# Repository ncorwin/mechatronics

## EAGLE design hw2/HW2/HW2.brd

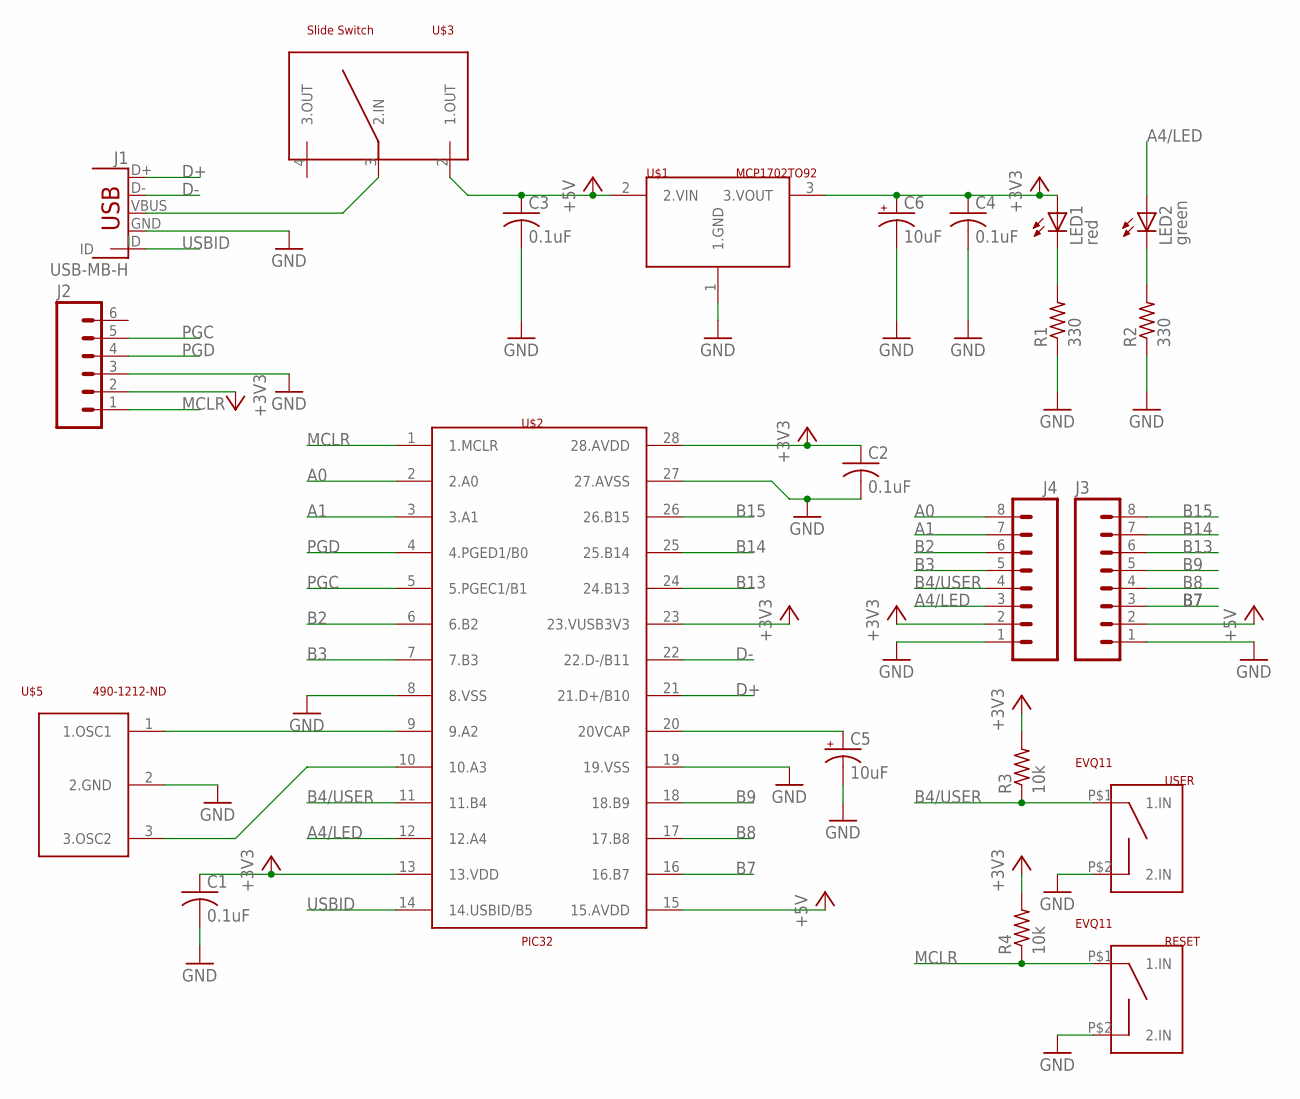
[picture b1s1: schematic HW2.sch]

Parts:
C1, C2, C3, C4: 0.1uF; C025-024X044
C5, C6: 10uF; B45181A
J1: USB-MB-H
J2: M06SILK_FEMALE_PTH; 1X06
J3, J4: M08SILK_FEMALE_PTH; 1X08
LED1: red; LED3MM
LED2: green; LED3MM
R1, R2: 330; 0204/7
R3, R4: 10k; 0204/7
RESET: EVQ11; 1X02_BIG
U$1: MCP1702TO92; TO92
U$2: PIC32; DIL28-3
U$3: A107673-ND; 1X05_NO_SILK
U$5: 490-1212-ND; 1X03_NO_SILK
USER: EVQ11; 1X02_BIG

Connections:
+3V3: C1.1, C2.1, C4.1, C6.+, J2.2, J4.2, LED1.A, R3.2, R4.2, U$1.3 (3.VOUT), U$2.13 (13.VDD), U$2.23 (23.VUSB3V3), U$2.28 (28.AVDD)
+5V: C3.1, J3.2, U$1.2 (2.VIN), U$2.15 (15.AVDD), U$3.2 (1.OUT)
A0: J4.8, U$2.2 (2.A0)
A1: J4.7, U$2.3 (3.A1)
A4/LED: J4.3, LED2.A, U$2.12 (12.A4)
B2: J4.6, U$2.6 (6.B2)
B3: J4.5, U$2.7 (7.B3)
B4/USER: J4.4, R3.1, U$2.11 (11.B4), USER.P$1 (1.IN)
B7: J3.3, U$2.16 (16.B7)
B8: J3.4, U$2.17 (17.B8)
B9: J3.5, U$2.18 (18.B9)
B13: J3.6, U$2.24 (24.B13)
B14: J3.7, U$2.25 (25.B14)
B15: J3.8, U$2.26 (26.B15)
D+: J1.D+, U$2.21 (21.D+/B10)
D-: J1.D-, U$2.22 (22.D-/B11)
GND: C1.2, C2.2, C3.2, C4.2, C5.-, C6.-, J1.GND, J2.3, J3.1, J4.1, R1.1, R2.1, RESET.P$2 (2.IN), U$1.1 (1.GND), U$2.8 (8.VSS), U$2.19 (19.VSS), U$2.27 (27.AVSS), U$5.2 (2.GND), USER.P$2 (2.IN)
MCLR: J2.1, R4.1, RESET.P$1 (1.IN), U$2.1 (1.MCLR)
unnamed: J1.VBUS, U$3.3 (2.IN)
unnamed: LED1.K (C), R1.2
unnamed: LED2.K (C), R2.2
unnamed: U$2.9 (9.A2), U$5.1 (1.OSC1)
unnamed: U$2.10 (10.A3), U$5.3 (3.OSC2)
unnamed: C5.+, U$2.20 (20VCAP)
PGC: J2.5, U$2.5 (5.PGEC1/B1)
PGD: J2.4, U$2.4 (4.PGED1/B0)
USBID: J1.ID, U$2.14 (14.USBID/B5)

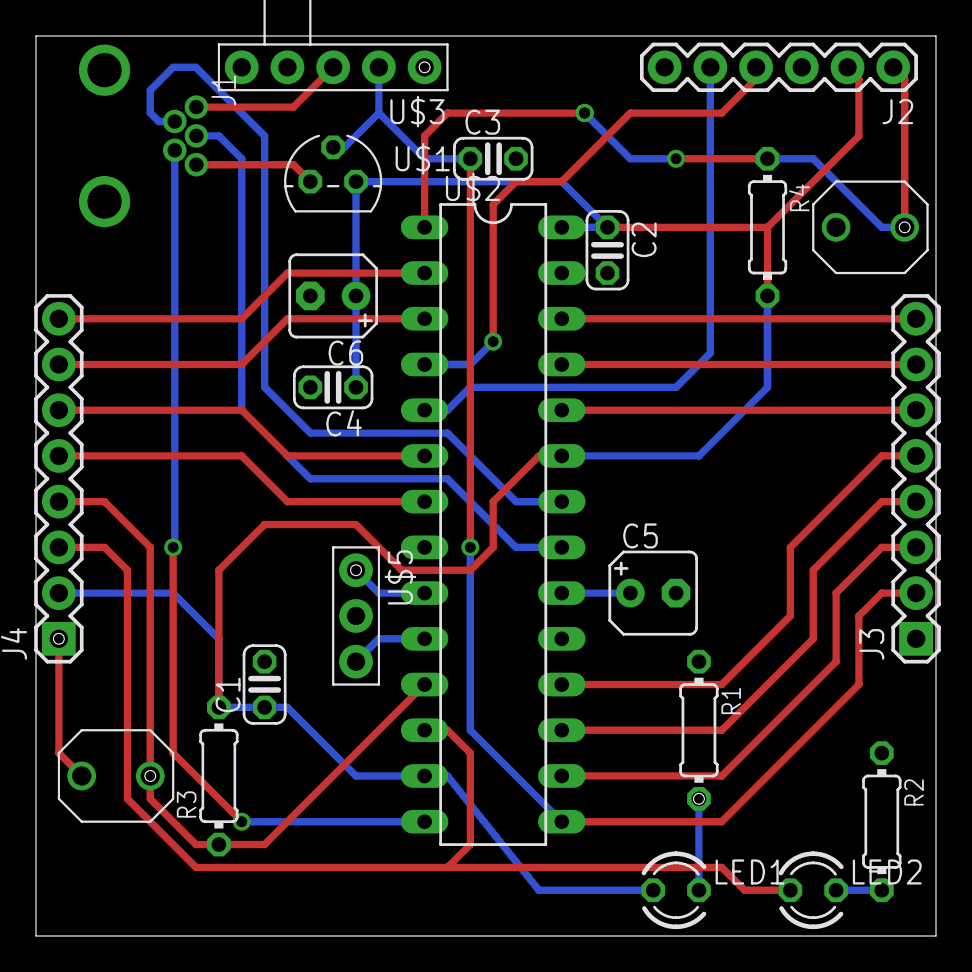
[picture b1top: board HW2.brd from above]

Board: 2 copper layers, 50.0 x 50.0 mm, 22 parts (0 on the bottom side), 27 nets.

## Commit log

2016-03-31 added screenshot of 3.3V power supply without caps
2016-03-31 added screenshot of 3.3V supply with caps. Oscilation stopped when 0.1 uF cap was added to regulator output
2016-04-02 Added picture of completed breadbord circuit
2016-04-02 Created main.c, can compile and upload but cant turn on LED
2016-04-02 still working on LED
2016-04-05 LED working, can toggle with pushbutton
2016-04-05 1 kHz toggle working, LED toggles at about 1 kHz, and turns on without toggling when pushbutton is depressed
2016-04-05 Pushbutton now pauses toggle at current LED output until released
2016-04-05 updated breadboard pic. Fixed wrong connection to crystal oscilator
2016-04-13 Created library for PCB
2016-04-14 Finished PCB schematic
2016-04-14 Working on .brd
2016-04-14 Finished .brd wiring
2016-04-14 Finished .brd
2016-04-14 Generated Gerber files
2016-04-14 Fixed Gerber files so it renders properly. zipped them into HW2.zip
2016-04-14 Added my name to the silkscreen layer
2016-04-14 Ready to be checked before order
2016-04-25 Created hw4 and started modifying example code
2016-04-25 Proboably finished spi.c
2016-04-25 created h file for configuring pic
2016-04-25 added waveform output to main.c
2016-04-25 it's not working
2016-04-25 it's still not working but I made separate .c and .h files for spi and i2c
2016-04-25 nothing's working. I give up
2016-04-25 spi is working, added nscope output pic
2016-04-25 fixed speed of DAC outputs
2016-04-26 working on I2C
2016-04-26 I2C still not working
2016-04-27 still working on I2C
2016-04-28 I2C working!
2016-04-28 Added pictures of hw4 circuit, made a pictures folder
2016-05-11 working on LCD
2016-05-11 still working on LCD
2016-05-12 hw5 LCD is working
2016-05-13 working on IMU
2016-05-14 still working on IMU, reading whoami wut not actual values
2016-05-16 still working on IMU
2016-05-17 IMU working
2016-05-17 added pictures to hw5, hw5 complete
2016-05-17 output OC1 and OC2 PWMs as functions of x and y accelration. Added picture of PWMs to repo. COmpleted hw6
2016-05-24 working on hw12, added code from repo, app crashes immediatly
2016-05-24 did hw9, FYI all android homeworks are in folders under android_projects/
2016-05-24 working on hw12, android camera line tracking, app still crashes immeadiatly
2016-05-29 created stl for wheel
2016-05-29 hw12 working for b&w image
2016-06-01 finished hw7, imu mouse
2016-06-01 completed hw8, CDC
2016-06-02 addd pictures
2016-06-02 changed hw 10 and 11 organization
2016-06-02 completed hw13 android cdc mostly'
2016-06-02 added pictures of addembled box and printed wheels
2016-06-02 added color tracking and ajustment to camera app
2016-06-05 motors are working, body is printing, working on android cdc communication
2016-06-05 camera + cdc app works, can change speed of motors
2016-06-05 added hw15 pic code to repo
2016-06-05 created hw16 folder, added cad model of robot body
2016-06-05 Finished hw13, android code is in android_project/hw13/, pic code and pictures in hw13/
2016-06-05 added cad of 4in wheel in case I need it
2016-06-07 fixed git I think
2016-06-08 final code used in demo
